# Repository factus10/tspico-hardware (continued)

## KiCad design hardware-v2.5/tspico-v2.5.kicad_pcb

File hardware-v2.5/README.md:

# TS-Pico v2.5 KiCad project

The v2.2 card (`../old/`, CircuitStudio, September 2023) redrawn all surface mount for JLCPCB assembly, on the v3 board outline (130 x 64.25 mm, 56 mm body plus the 8.25 mm tongue, same edge connector, 4 layers). The circuit, the designators and the Pico pin map are v2.2's, so the shipped firmware (tspico-firmware-build) runs unchanged. One block is new: bench programming of the flash from the Pico, so a board with a blank soldered flash can be loaded without a ROM programmer or a 2068.

**To order:** the JLCPCB upload files (Gerber zip, BOM, placement), ordering notes, schematic PDF and renders are on the [v2.5-proto1 release](https://github.com/factus10/tspico-hardware/releases/tag/v2.5-proto1). To regenerate them from this folder, run `python3 scripts/gen_fab.py` (output in `fab/jlcpcb/`).

Status 2026-10-11: schematic ERC clean and board DRC clean at every severity (no errors, no warnings, nothing unconnected); `scripts/check.sh` passes. Fully routed by `flow.py` on its first attempt with no hand edits: 2496 track segments and 406 vias (all 0.6/0.3 mm), every track on F.Cu or B.Cu, so both planes are unbroken; narrowest track 0.13 mm. Fab outputs (Gerbers, JLC BOM and CPL) are generated by `scripts/gen_fab.py`. Not built. JLC parts plus loading fees: $23.92 per board on a 10-board run, of which the Pico, flash and SRAM are $16.29.

## What changed from v2.2

| Part | v2.2 | v2.5 |
|---|---|---|
| U2 Pico | on socket headers | Raspberry Pi Pico module reflowed on its castellations (LCSC C7203002); a Pico 2 fits the footprint |
| U10 flash | SST39SF040 DIP-32 | SST39SF040 PLCC-32, soldered |
| U13 SRAM | AS6C4008 DIP-32 | CY62148ELL-55SXI (or AS6C4008-55SIN), 450 mil SOIC-32 |
| U1, U4, U5, U8, U9 | 74LS DIP | 74LS SOIC (same families: Pico 3.3 V outputs need TTL thresholds) |
| U6, U7 | 74LVC245 DIP | 74LVC245APW TSSOP-20 |
| U11 | TLC555 DIP | NE555 SOIC-8 (JLC preferred part, no loading fee) |
| Q1, D2 | 2N3904, SB260 | MMBT3904, SS14 |
| C2, C12, C16 | 10 uF electrolytic | 10 uF 25 V X5R 0805 (the 25 V rating keeps DC-bias loss small at 5 V, which matters for the 2.4 s reset timing cap C12) |
| U3 SD | SD breakout module | HRO TF-01A push-push socket (as v3), 10 k pull-ups on DAT1/DAT2 |
| SW1-SW3 | through-hole tactile | TS-1187A SMD tactile |
| JP1 (/BE link), P10 (flash write enable) | 2-pin header + shunt | solder jumper, closed as shipped (cut to open) |
| JP4 (port $00-$0F / $10-$1F) | 3-pin header | 3-pad solder jumper, 1-2 ($00-$0F) as shipped |
| JP2, JP3, JP5 (external NMI, TS reset, Pico reset buttons) | 2-pin headers | DNP SMD header pads |
| R12 | (rework on built boards, not in the 2023 schematic) | 4.7 k from U6 pin 8 (D6) to pin 10 (GND) |
| new | | R13/R14 10 k pull-ups on /ROSCS and /IORQ, R15/R16 10 k pull-ups on the flash and SRAM /CE (both deselected while the Pico boots) |
| new | | bench programming, below |

Everything JLCPCB assembles is SMT on the top side. Nothing through-hole is left.

## Bench programming the flash

The shipped firmware maps the 2068's HOME ROM from flash unconditionally at power-on (`src/dev_tspico.py`, `set_ctrl` started at line 5693), and `flash/README.md` says new boards get the 512K image burned with a programmer. A soldered blank flash would therefore leave the 2068 unable to boot, and the in-place `romupdate.tap` path needs a working ROM first. v2.2 has no free Pico GPIO to drive the flash address bus, so v2.5 adds a shift-register path that reuses existing pins:

- U12, U14, U15: 74HCT595 chain. SER = D1_L (GP3), SRCLK = D0_L (GP2) (the SPI0 pins already used for the SD card), RCLK = SD_CS (GP28). U12 drives A0-A7, U14 A8-A13, /RD and the flash /WE, U15 drives D0-D7 through RN1/RN2 (4.7 k). A14/A15 come from the Pico through U8 (R13 holds /ROSCS high off the bus), A16-A18 and /CE as in v2.2.
- Read-back for verify: U15's outputs high, /RD low, U6 enabled. R14 holds /IORQ high, so U6 points at the Pico, and the byte arrives on GP2-GP9. The 4.7 k series resistors let the flash win against U15.
- Power: SW4 (slide switch, RUN/PROG) in PROG puts the Pico's USB VBUS on the card's +5V through D3, so the memories and logic run with the card out of the computer.
- Enable: the 595 outputs are on only when SW4 is in PROG, VBUS is present, and there is no +15 V on edge pin B3 (Q2/Q3). Plugged into a powered 2068 they stay off whatever the switch says. In the 2068, SD traffic clocks garbage into the chain, but the outputs are disabled, so nothing reaches the bus.
- Procedure: card out of the 2068, SW4 to PROG, USB to the Pico, copy the 512K image to the Pico as `/flash.rom`, run `tools/benchprog.py` (draft, untested: chip erase, byte program, verify; a few minutes in MicroPython). SW4 back to RUN before the card goes into the computer.

The Z80-side `romupdate.tap` path works exactly as on v2.2 (P10 closed).

Things to keep in mind: with SW4 in PROG and USB plugged into a 2068 that is switched off, the USB port would try to power the 2068's 5 V rail (D3 conducts). The port's current limit protects the host, but keep SW4 in RUN except on the bench. The card's rail sits at about 4.7 V in PROG mode (USB minus a Schottky), which is inside the flash's 4.5-5.5 V range and fine for LS logic at bench temperatures.

## Files

| File | Purpose |
|---|---|
| `tspico-v2.5.kicad_pro`, `.kicad_sch`, `.kicad_pcb` | Project, root sheet, board. Sheets: `interface`, `logic`, `memory`, `pico`, `benchprog`. |
| `scripts/gen_schematic.py` | Generates the root sheet and the five sheets (netlist style: a global label on every pin, as in v3) and the project symbols (edge connector, plus corrected copies of the Pico, 74LVC245 and MMBT3904 stock symbols so ERC judges pin types correctly). Overwrites hand edits. |
| `scripts/parts.py` | (Value, footprint) to MPN and LCSC number, stamped on every symbol. Priced 2026-10-11 with `jlc_price.py`. |
| `scripts/gen_board.py`, `gen_edge_symbol.py` | Board skeleton and edge connector, shared geometry with v3 (`../hardware/README.md`). |
| `scripts/gen_layout.py` | Placement table, planes (In1 GND, In2 +5V; +3V3 is routed). Overwrites the board. |
| `scripts/flow.py`, `autoroute.py`, `finish.py`, `finish_route.py`, `silk.py` | The v3 routing flow (Freerouting 2.4.1, then clean-up and silkscreen), with v2.5's plane nets. |
| `scripts/gen_fab.py` | Gerbers, drill, JLC BOM and CPL into `fab/jlcpcb/`. |
| `scripts/check.sh` | ERC and DRC, fails on any violation. |
| `tools/benchprog.py` | Draft MicroPython bench programmer. |

```bash
cd hardware-v2.5
PY=/Applications/KiCad/KiCad.app/Contents/Frameworks/Python.framework/Versions/Current/bin/python3
python3 scripts/gen_schematic.py
$PY scripts/flow.py --jar <freerouting-2.4.1.jar>
python3 scripts/gen_fab.py
scripts/check.sh
```

## Layout

The Pico sits along the top left with its USB out of the left edge. Its GP0-GP15 row faces down toward the logic. Above it, left to right: SW4 and D3 by VBUS, D2/C2 by VSYS, then the Pico-side pull-ups. The buttons are along the top edge (SW1 NMI, SW2 TS reset, SW3 Pico reset), each with its DNP external-button pads. The SRAM and flash sit in the middle band, and the 555 reset is in the top-right corner. The micro SD is on the left edge below the Pico, its shell flush with the edge. The glue row (U1, U5, U4, U9, U8, U7) and the two address 595s (U12, U14) run across the board, with Q2/Q3 (the program-enable interlock) at its right end. U6 sits over the data fingers, and the data 595 (U15) with RN1/RN2 sits at the left end of the fingers. An earlier placement with U15 at the far end of the 595 row left one of its eight outputs unroutable twice.

Every used bottom-side finger (address, +15 V, +5 V, GND, /BE_IN) gets a locked B.Cu stub and a via 1.4 mm into the body (`gen_layout.py`); +5V gets two vias and a 0.5 mm stub into the In2 plane. Without them the router boxed in B4 (+5V) and B13 (A3).

## Before ordering

- Stock: U10 (C632847, 17 at JLC), U13 (C511135, 16), U9 (C7731, 56). Consign or swap if short; AS6C4008-55SIN fits U13's footprint and pinout.
- U13: check the CY62148E SOIC-32 pinout against the datasheet: /CE pin 22, /OE pin 24, /WE pin 29, VCC 32, GND 16. Address and data order do not matter for an SRAM only the Z80 sees.
- TF-01A footprint and card-detect: same open items as v3 (`../hardware/README.md`).
- JLC rotations for the PLCC, SOICs, Pico module and switches in the placement preview.

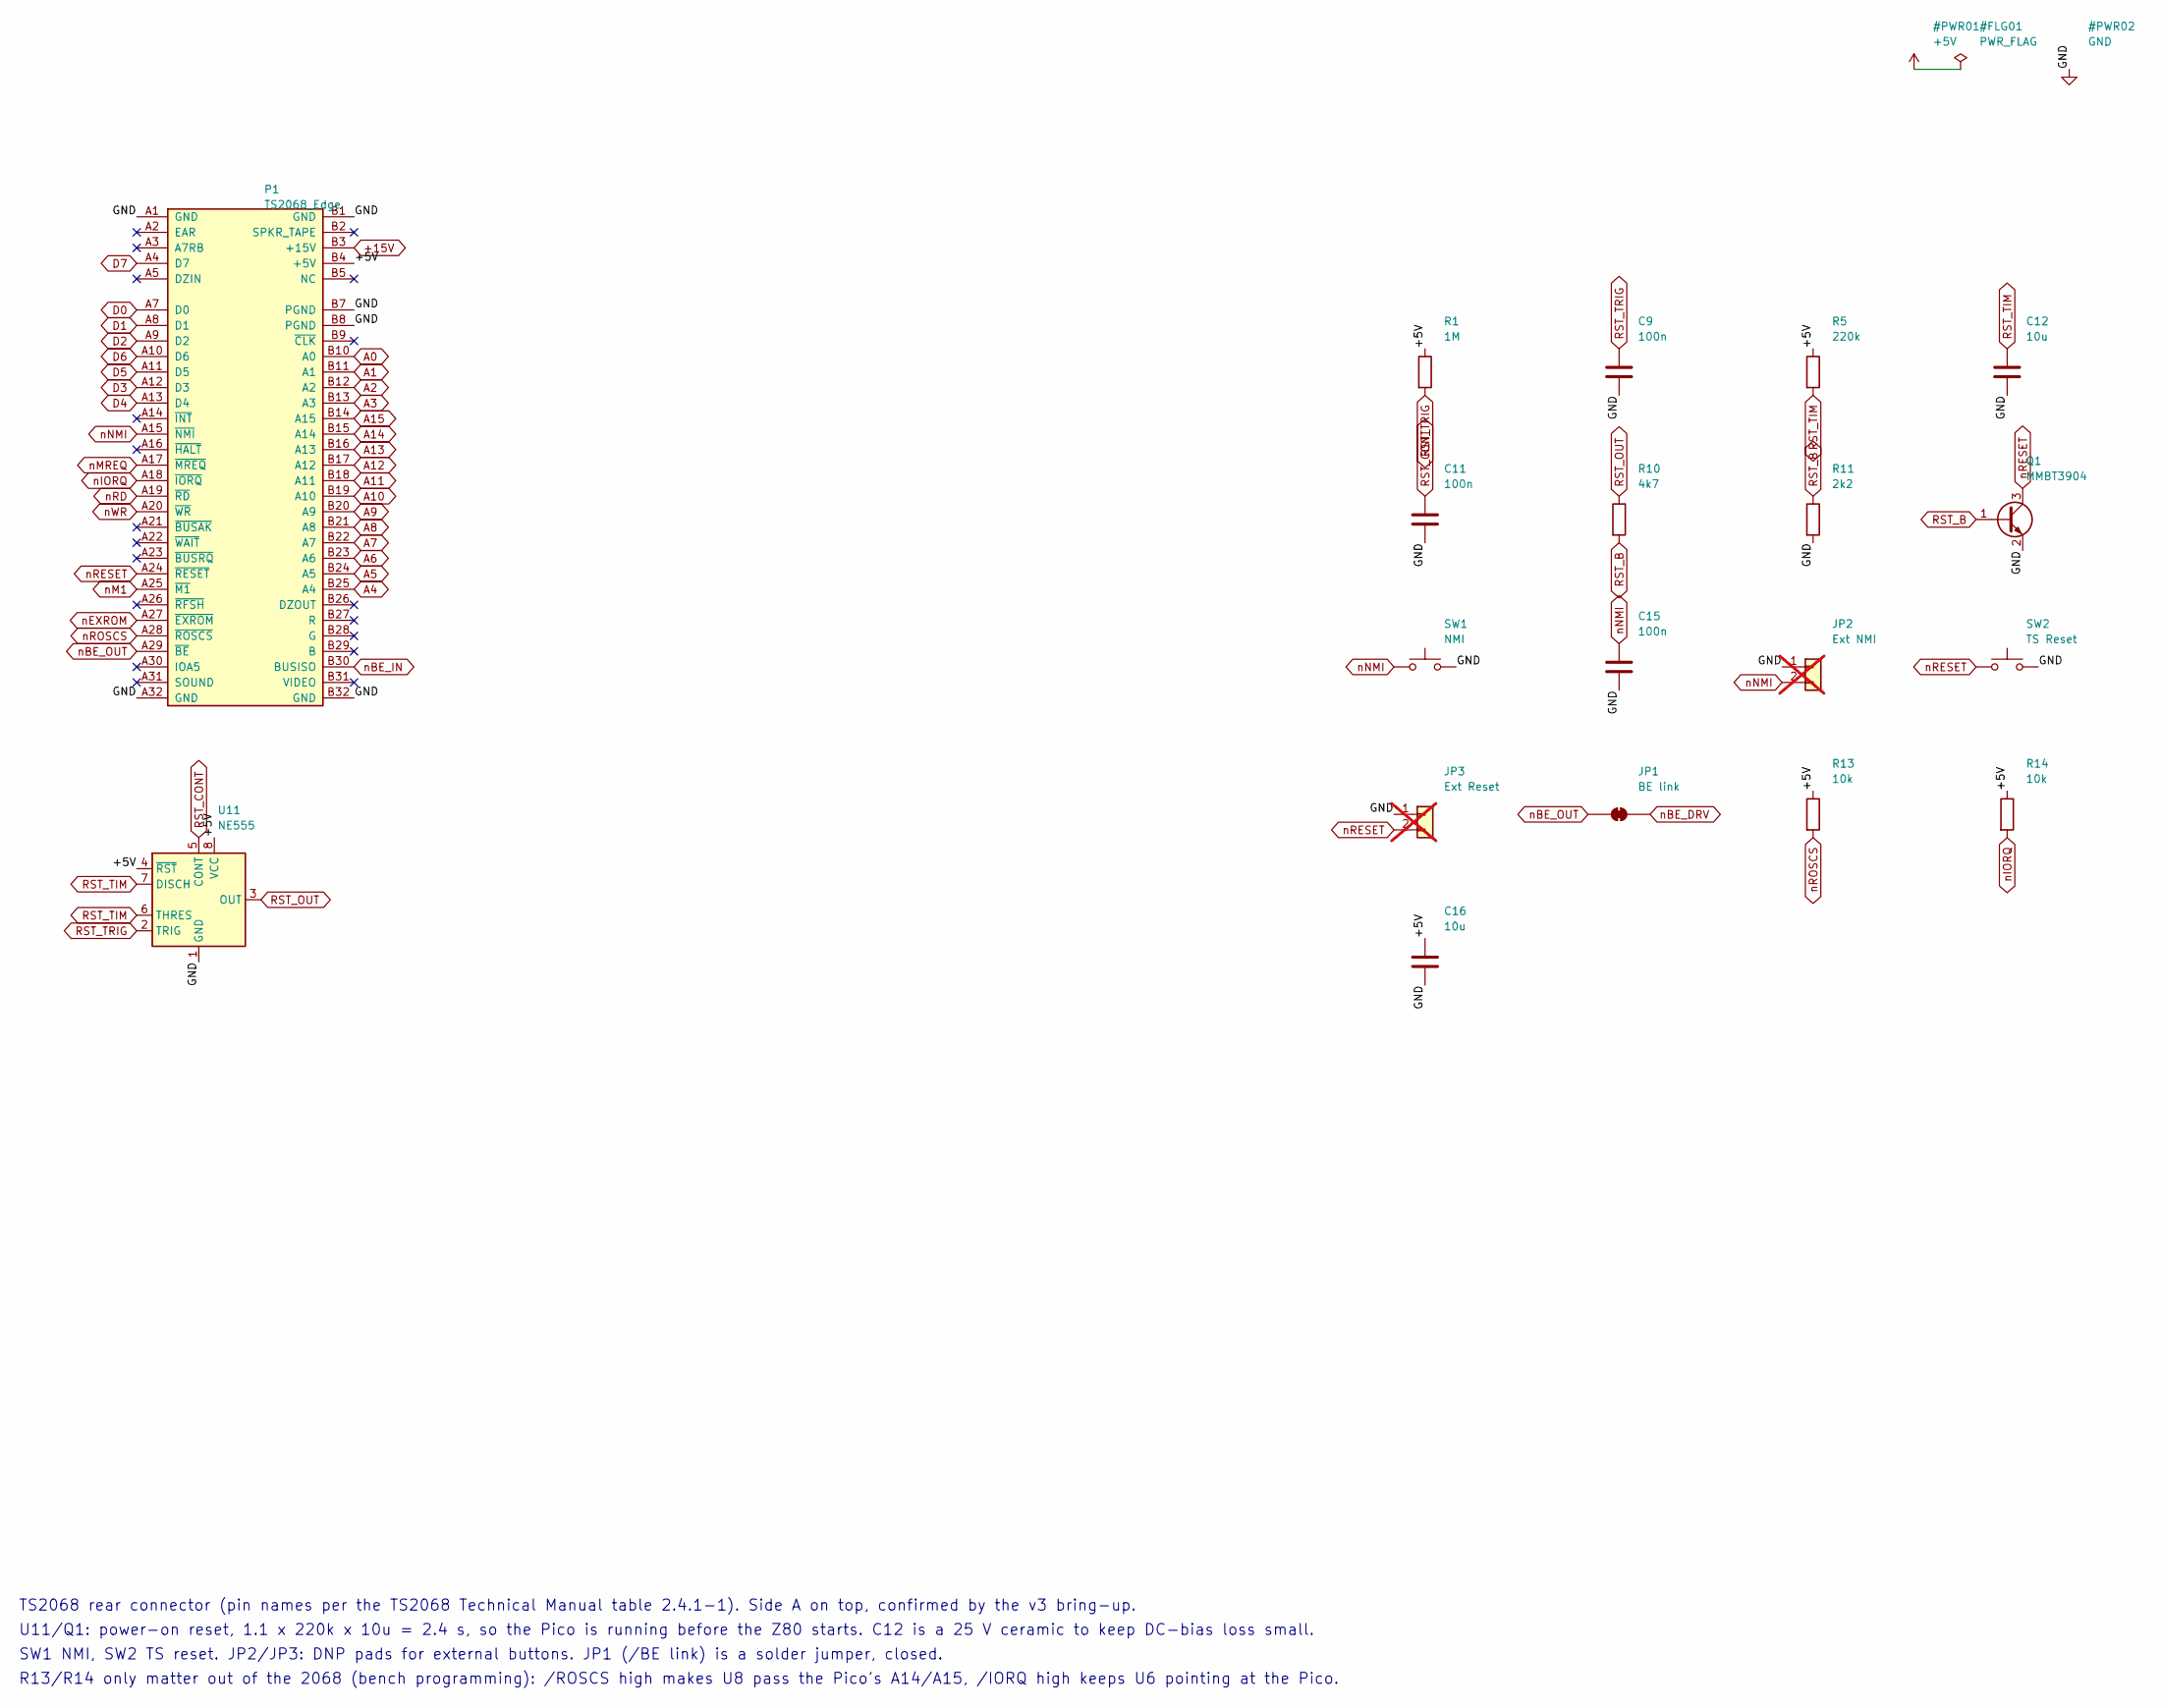
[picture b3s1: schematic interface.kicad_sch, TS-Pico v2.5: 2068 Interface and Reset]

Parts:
C9, C11, C15: 100n; C_0603_1608Metric; MPN CC0603KRX7R9BB104; LCSC C14663
C12, C16: 10u; C_0805_2012Metric; MPN CL21A106KAYNNNE; LCSC C15850
JP1: BE link; SolderJumper-2_P1.3mm_Bridged_RoundedPad1.0x1.5mm
JP2: Ext NMI; PinHeader_1x02_P2.54mm_Vertical_SMD_Pin1Left; not fitted
JP3: Ext Reset; PinHeader_1x02_P2.54mm_Vertical_SMD_Pin1Left; not fitted
P1: TS2068_Edge; TS2068_EdgeConnector_2x32
Q1: MMBT3904; SOT-23; MPN MMBT3904; LCSC C20526
R1: 1M; R_0603_1608Metric; MPN 0603WAF1004T5E; LCSC C22935
R5: 220k; R_0603_1608Metric; MPN 0603WAF2203T5E; LCSC C22961
R10: 4k7; R_0603_1608Metric; MPN 0603WAF4701T5E; LCSC C23162
R11: 2k2; R_0603_1608Metric; MPN 0603WAF2201T5E; LCSC C4190
R13, R14: 10k; R_0603_1608Metric; MPN 0603WAF1002T5E; LCSC C25804
SW1: NMI; SW_Push_1P1T_XKB_TS-1187A; MPN TS-1187A-B-A-B; LCSC C318884
SW2: TS Reset; SW_Push_1P1T_XKB_TS-1187A; MPN TS-1187A-B-A-B; LCSC C318884
U11: NE555; SOIC-8_3.9x4.9mm_P1.27mm; MPN NE555DR; LCSC C7593

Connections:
+5V: C16.1, P1.B4 (+5V), R1.1, R5.1, R13.1, R14.1, U11.4 (~RST), U11.8 (VCC); also elsewhere on the board
+15V: P1.B3 (+15V); also elsewhere on the board
A0: P1.B10 (A0); also elsewhere on the board
A1: P1.B11 (A1); also elsewhere on the board
A2: P1.B12 (A2); also elsewhere on the board
A3: P1.B13 (A3); also elsewhere on the board
A4: P1.B25 (A4); also elsewhere on the board
A5: P1.B24 (A5); also elsewhere on the board
A6: P1.B23 (A6); also elsewhere on the board
A7: P1.B22 (A7); also elsewhere on the board
A8: P1.B21 (A8); also elsewhere on the board
A9: P1.B20 (A9); also elsewhere on the board
A10: P1.B19 (A10); also elsewhere on the board
A11: P1.B18 (A11); also elsewhere on the board
A12: P1.B17 (A12); also elsewhere on the board
A13: P1.B16 (A13); also elsewhere on the board
A14: P1.B15 (A14); also elsewhere on the board
A15: P1.B14 (A15); also elsewhere on the board
D0: P1.A7 (D0); also elsewhere on the board
D1: P1.A8 (D1); also elsewhere on the board
D2: P1.A9 (D2); also elsewhere on the board
D3: P1.A12 (D3); also elsewhere on the board
D4: P1.A13 (D4); also elsewhere on the board
D5: P1.A11 (D5); also elsewhere on the board
D6: P1.A10 (D6); also elsewhere on the board
D7: P1.A4 (D7); also elsewhere on the board
GND: C9.2, C11.2, C12.2, C15.2, C16.2, JP2.1, JP3.1, P1.A1 (GND), P1.A32 (GND), P1.B1 (GND), P1.B7 (PGND), P1.B8 (PGND), P1.B32 (GND), Q1.2 (E), R11.2, SW1.2, SW2.2, U11.1 (GND); also elsewhere on the board
RST_B: Q1.1 (B), R10.2, R11.1
RST_CONT: C11.1, U11.5 (CONT)
RST_OUT: R10.1, U11.3 (OUT)
RST_TIM: C12.1, R5.2, U11.6 (THRES), U11.7 (DISCH)
RST_TRIG: C9.1, R1.2, U11.2 (TRIG)
nBE_DRV: JP1.2 (B); also elsewhere on the board
nBE_IN: P1.B30 (BUSISO); also elsewhere on the board
nBE_OUT: JP1.1 (A), P1.A29 (~BE)
nEXROM: P1.A27 (~EXROM); also elsewhere on the board
nIORQ: P1.A18 (~IORQ), R14.2; also elsewhere on the board
nM1: P1.A25 (~M1); also elsewhere on the board
nMREQ: P1.A17 (~MREQ); also elsewhere on the board
nNMI: C15.1, JP2.2, P1.A15 (~NMI), SW1.1
nRD: P1.A19 (~RD); also elsewhere on the board
nRESET: JP3.2, P1.A24 (~RESET), Q1.3 (C), SW2.1
nROSCS: P1.A28 (~ROSCS), R13.2; also elsewhere on the board
nWR: P1.A20 (~WR); also elsewhere on the board

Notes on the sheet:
TS2068 rear connector (pin names per the TS2068 Technical Manual table 2.4.1-1). Side A on top, confirmed by the v3 bring-up.
U11/Q1: power-on reset, 1.1 x 220k x 10u = 2.4 s, so the Pico is running before the Z80 starts. C12 is a 25 V ceramic to keep DC-bias loss small.
SW1 NMI, SW2 TS reset. JP2/JP3: DNP pads for external buttons. JP1 (/BE link) is a solder jumper, closed.
R13/R14 only matter out of the 2068 (bench programming): /ROSCS high makes U8 pass the Pico's A14/A15, /IORQ high keeps U6 pointing at the Pico.

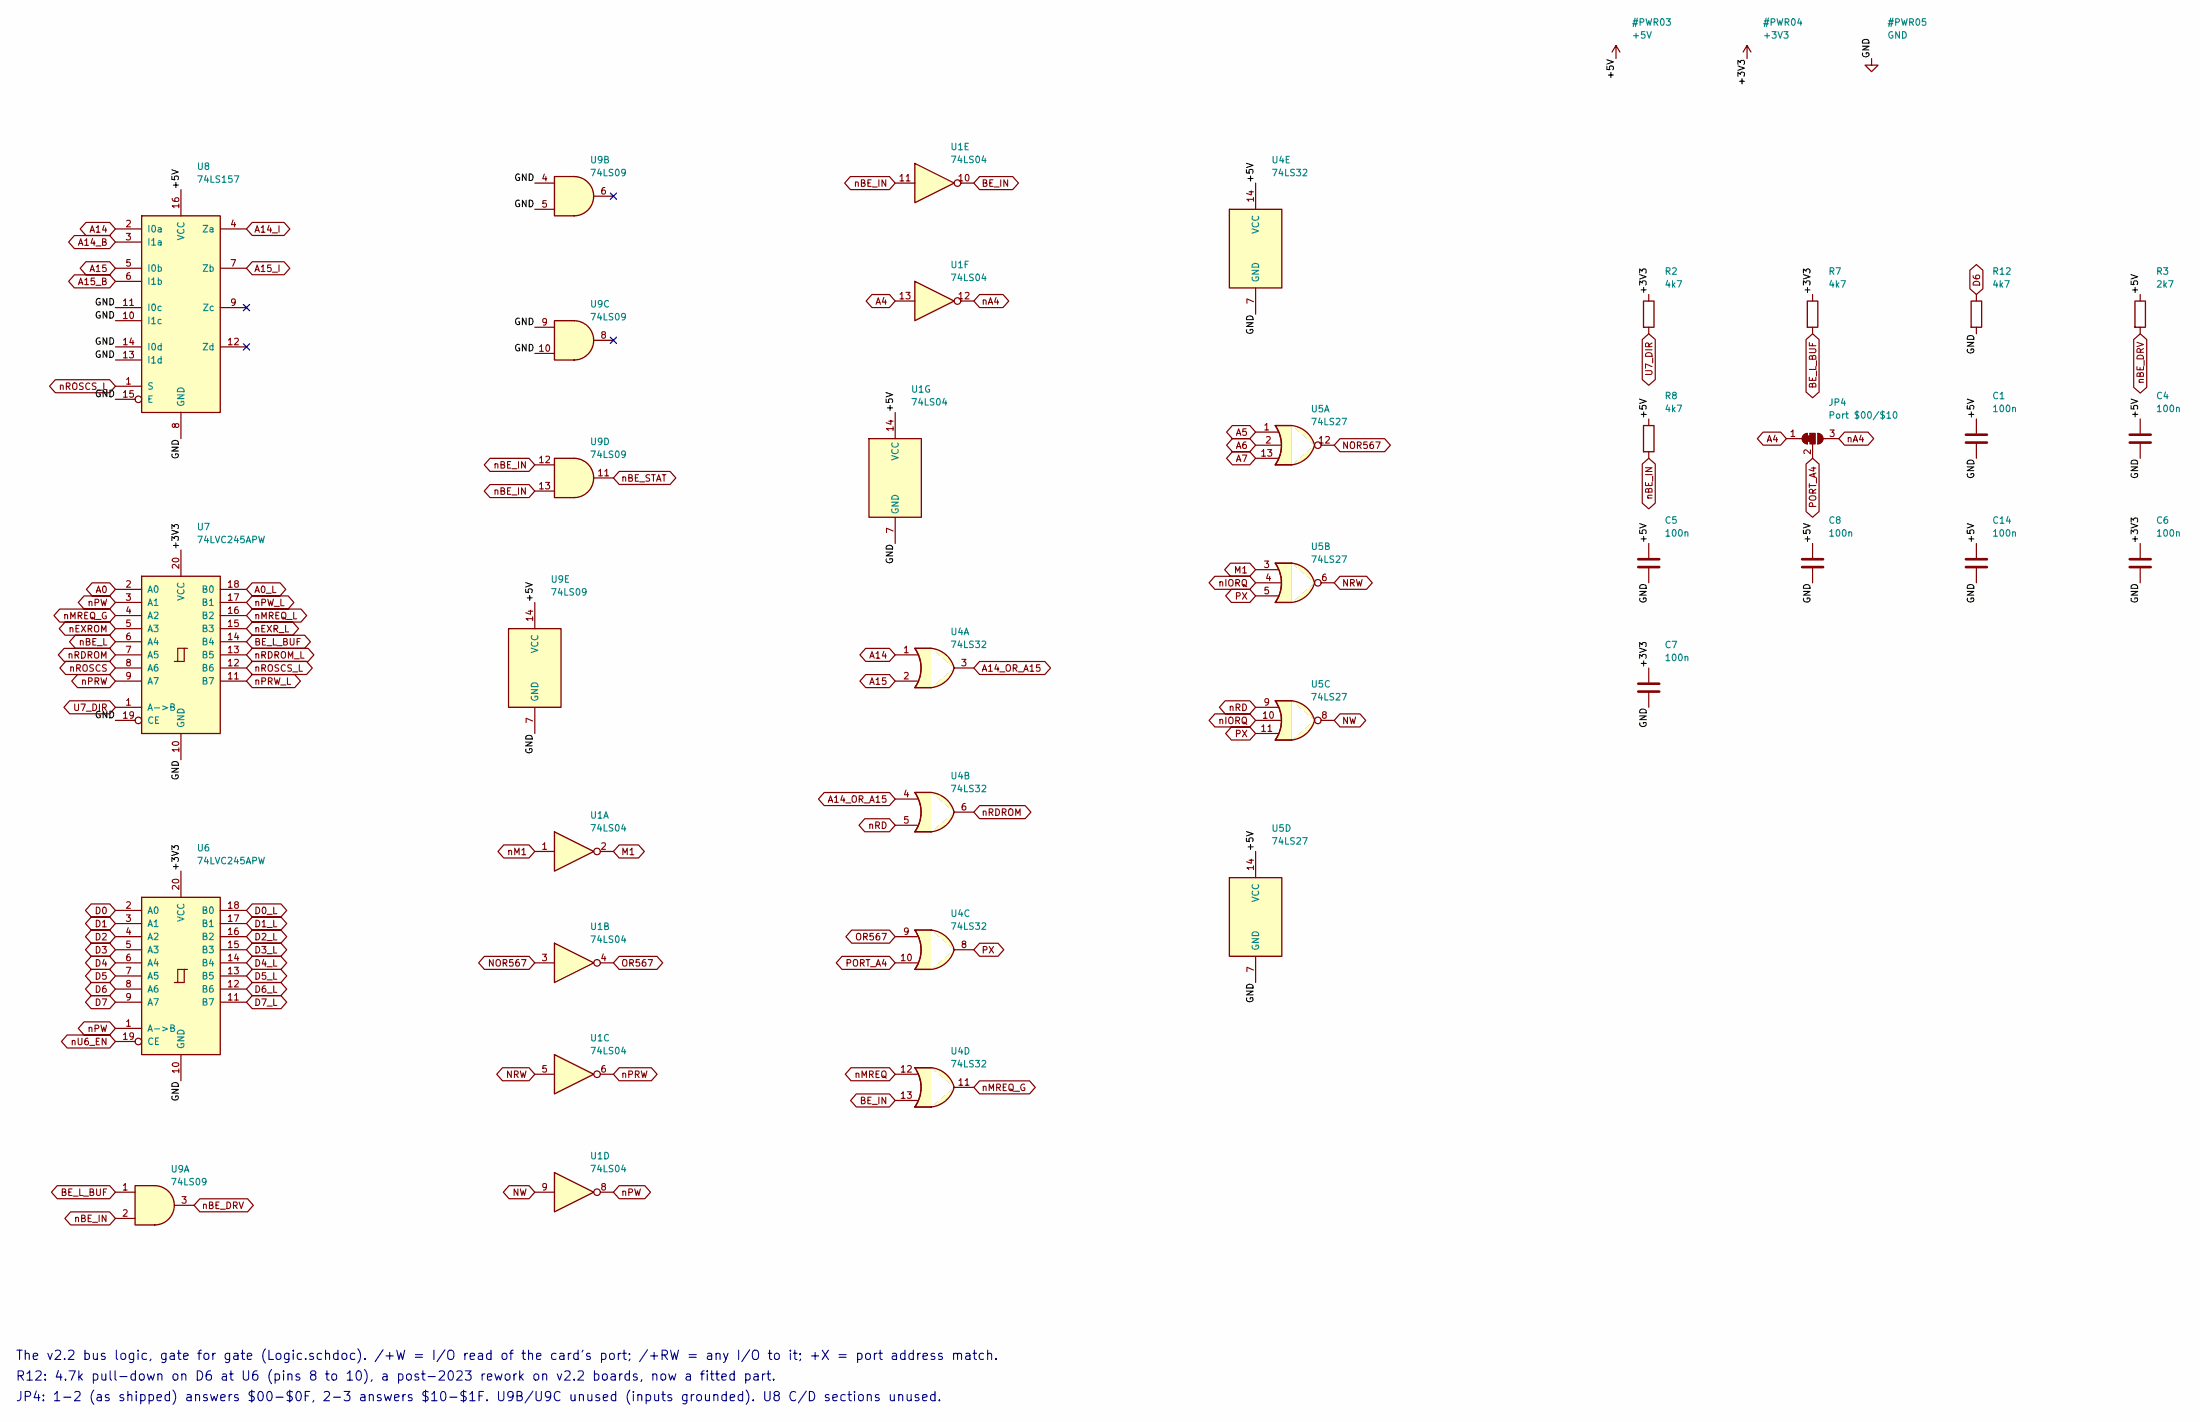
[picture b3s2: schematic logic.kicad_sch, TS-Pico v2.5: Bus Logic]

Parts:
C1, C4, C5, C6, C7, C8, C14: 100n; C_0603_1608Metric; MPN CC0603KRX7R9BB104; LCSC C14663
JP4: Port $00/$10; SolderJumper-3_P1.3mm_Bridged12_RoundedPad1.0x1.5mm_NumberL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
R2, R7, R8, R12: 4k7; R_0603_1608Metric; MPN 0603WAF4701T5E; LCSC C23162
R3: 2k7; R_0603_1608Metric; MPN 0603WAF2701T5E; LCSC C13167
U1: 74LS04; SOIC-14_3.9x8.7mm_P1.27mm; MPN SN74LS04DR; LCSC C6796
U4: 74LS32; SOIC-14_3.9x8.7mm_P1.27mm; MPN SN74LS32DR; LCSC C116812
U5: 74LS27; SOIC-14_3.9x8.7mm_P1.27mm; MPN XL74LS27; LCSC C707098
U6, U7: 74LVC245APW; TSSOP-20_4.4x6.5mm_P0.65mm; MPN 74LVC245APW,118; LCSC C6082
U8: 74LS157; SOIC-16_3.9x9.9mm_P1.27mm; MPN XL74LS157; LCSC C707097
U9: 74LS09; SOIC-14_3.9x8.7mm_P1.27mm; MPN SN74LS09DR; LCSC C7731

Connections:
+3V3: C6.1, C7.1, R2.1, R7.1, U6.20 (VCC), U7.20 (VCC); also elsewhere on the board
+5V: C1.1, C4.1, C5.1, C8.1, C14.1, R3.1, R8.1, U1.14 (VCC), U4.14 (VCC), U5.14 (VCC), U8.16 (VCC), U9.14 (VCC); also elsewhere on the board
A0: U7.2 (A0); also elsewhere on the board
A0_L: U7.18 (B0); also elsewhere on the board
A4: JP4.1 (A), U1.13; also elsewhere on the board
A5: U5.1; also elsewhere on the board
A6: U5.2; also elsewhere on the board
A7: U5.13; also elsewhere on the board
A14: U4.1, U8.2 (I0a); also elsewhere on the board
A14_B: U8.3 (I1a); also elsewhere on the board
A14_I: U8.4 (Za); also elsewhere on the board
A14_OR_A15: U4.3, U4.4
A15: U4.2, U8.5 (I0b); also elsewhere on the board
A15_B: U8.6 (I1b); also elsewhere on the board
A15_I: U8.7 (Zb); also elsewhere on the board
BE_IN: U1.10, U4.13
BE_L_BUF: R7.2, U7.14 (B4), U9.1
D0: U6.2 (A0); also elsewhere on the board
D0_L: U6.18 (B0); also elsewhere on the board
D1: U6.3 (A1); also elsewhere on the board
D1_L: U6.17 (B1); also elsewhere on the board
D2: U6.4 (A2); also elsewhere on the board
D2_L: U6.16 (B2); also elsewhere on the board
D3: U6.5 (A3); also elsewhere on the board
D3_L: U6.15 (B3); also elsewhere on the board
D4: U6.6 (A4); also elsewhere on the board
D4_L: U6.14 (B4); also elsewhere on the board
D5: U6.7 (A5); also elsewhere on the board
D5_L: U6.13 (B5); also elsewhere on the board
D6: R12.1, U6.8 (A6); also elsewhere on the board
D6_L: U6.12 (B6); also elsewhere on the board
D7: U6.9 (A7); also elsewhere on the board
D7_L: U6.11 (B7); also elsewhere on the board
GND: C1.2, C4.2, C5.2, C6.2, C7.2, C8.2, C14.2, R12.2, U1.7 (GND), U4.7 (GND), U5.7 (GND), U6.10 (GND), U7.10 (GND), U7.19 (CE), U8.8 (GND), U8.10 (I1c), U8.11 (I0c), U8.13 (I1d), U8.14 (I0d), U8.15 (E), U9.4, U9.5, U9.7 (GND), U9.9, U9.10; also elsewhere on the board
M1: U1.2, U5.3
NOR567: U1.3, U5.12
NRW: U1.5, U5.6
NW: U1.9, U5.8
OR567: U1.4, U4.9
PORT_A4: JP4.2 (C), U4.10
PX: U4.8, U5.5, U5.11
U7_DIR: R2.2, U7.1 (A->B)
nA4: JP4.3 (B), U1.12
nBE_DRV: R3.2, U9.3; also elsewhere on the board
nBE_IN: R8.2, U1.11, U9.2, U9.12, U9.13; also elsewhere on the board
nBE_L: U7.6 (A4); also elsewhere on the board
nBE_STAT: U9.11; also elsewhere on the board
nEXROM: U7.5 (A3); also elsewhere on the board
nEXR_L: U7.15 (B3); also elsewhere on the board
nIORQ: U5.4, U5.10; also elsewhere on the board
nM1: U1.1; also elsewhere on the board
nMREQ: U4.12; also elsewhere on the board
nMREQ_G: U4.11, U7.4 (A2)
nMREQ_L: U7.16 (B2); also elsewhere on the board
nPRW: U1.6, U7.9 (A7)
nPRW_L: U7.11 (B7); also elsewhere on the board
nPW: U1.8, U6.1 (A->B), U7.3 (A1)
nPW_L: U7.17 (B1); also elsewhere on the board
nRD: U4.5, U5.9; also elsewhere on the board
nRDROM: U4.6, U7.7 (A5)
nRDROM_L: U7.13 (B5); also elsewhere on the board
nROSCS: U7.8 (A6); also elsewhere on the board
nROSCS_L: U7.12 (B6), U8.1 (S); also elsewhere on the board
nU6_EN: U6.19 (CE); also elsewhere on the board

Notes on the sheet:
The v2.2 bus logic, gate for gate (Logic.schdoc). /+W = I/O read of the card's port; /+RW = any I/O to it; +X = port address match.
R12: 4.7k pull-down on D6 at U6 (pins 8 to 10), a post-2023 rework on v2.2 boards, now a fitted part.
JP4: 1-2 (as shipped) answers $00-$0F, 2-3 answers $10-$1F. U9B/U9C unused (inputs grounded). U8 C/D sections unused.

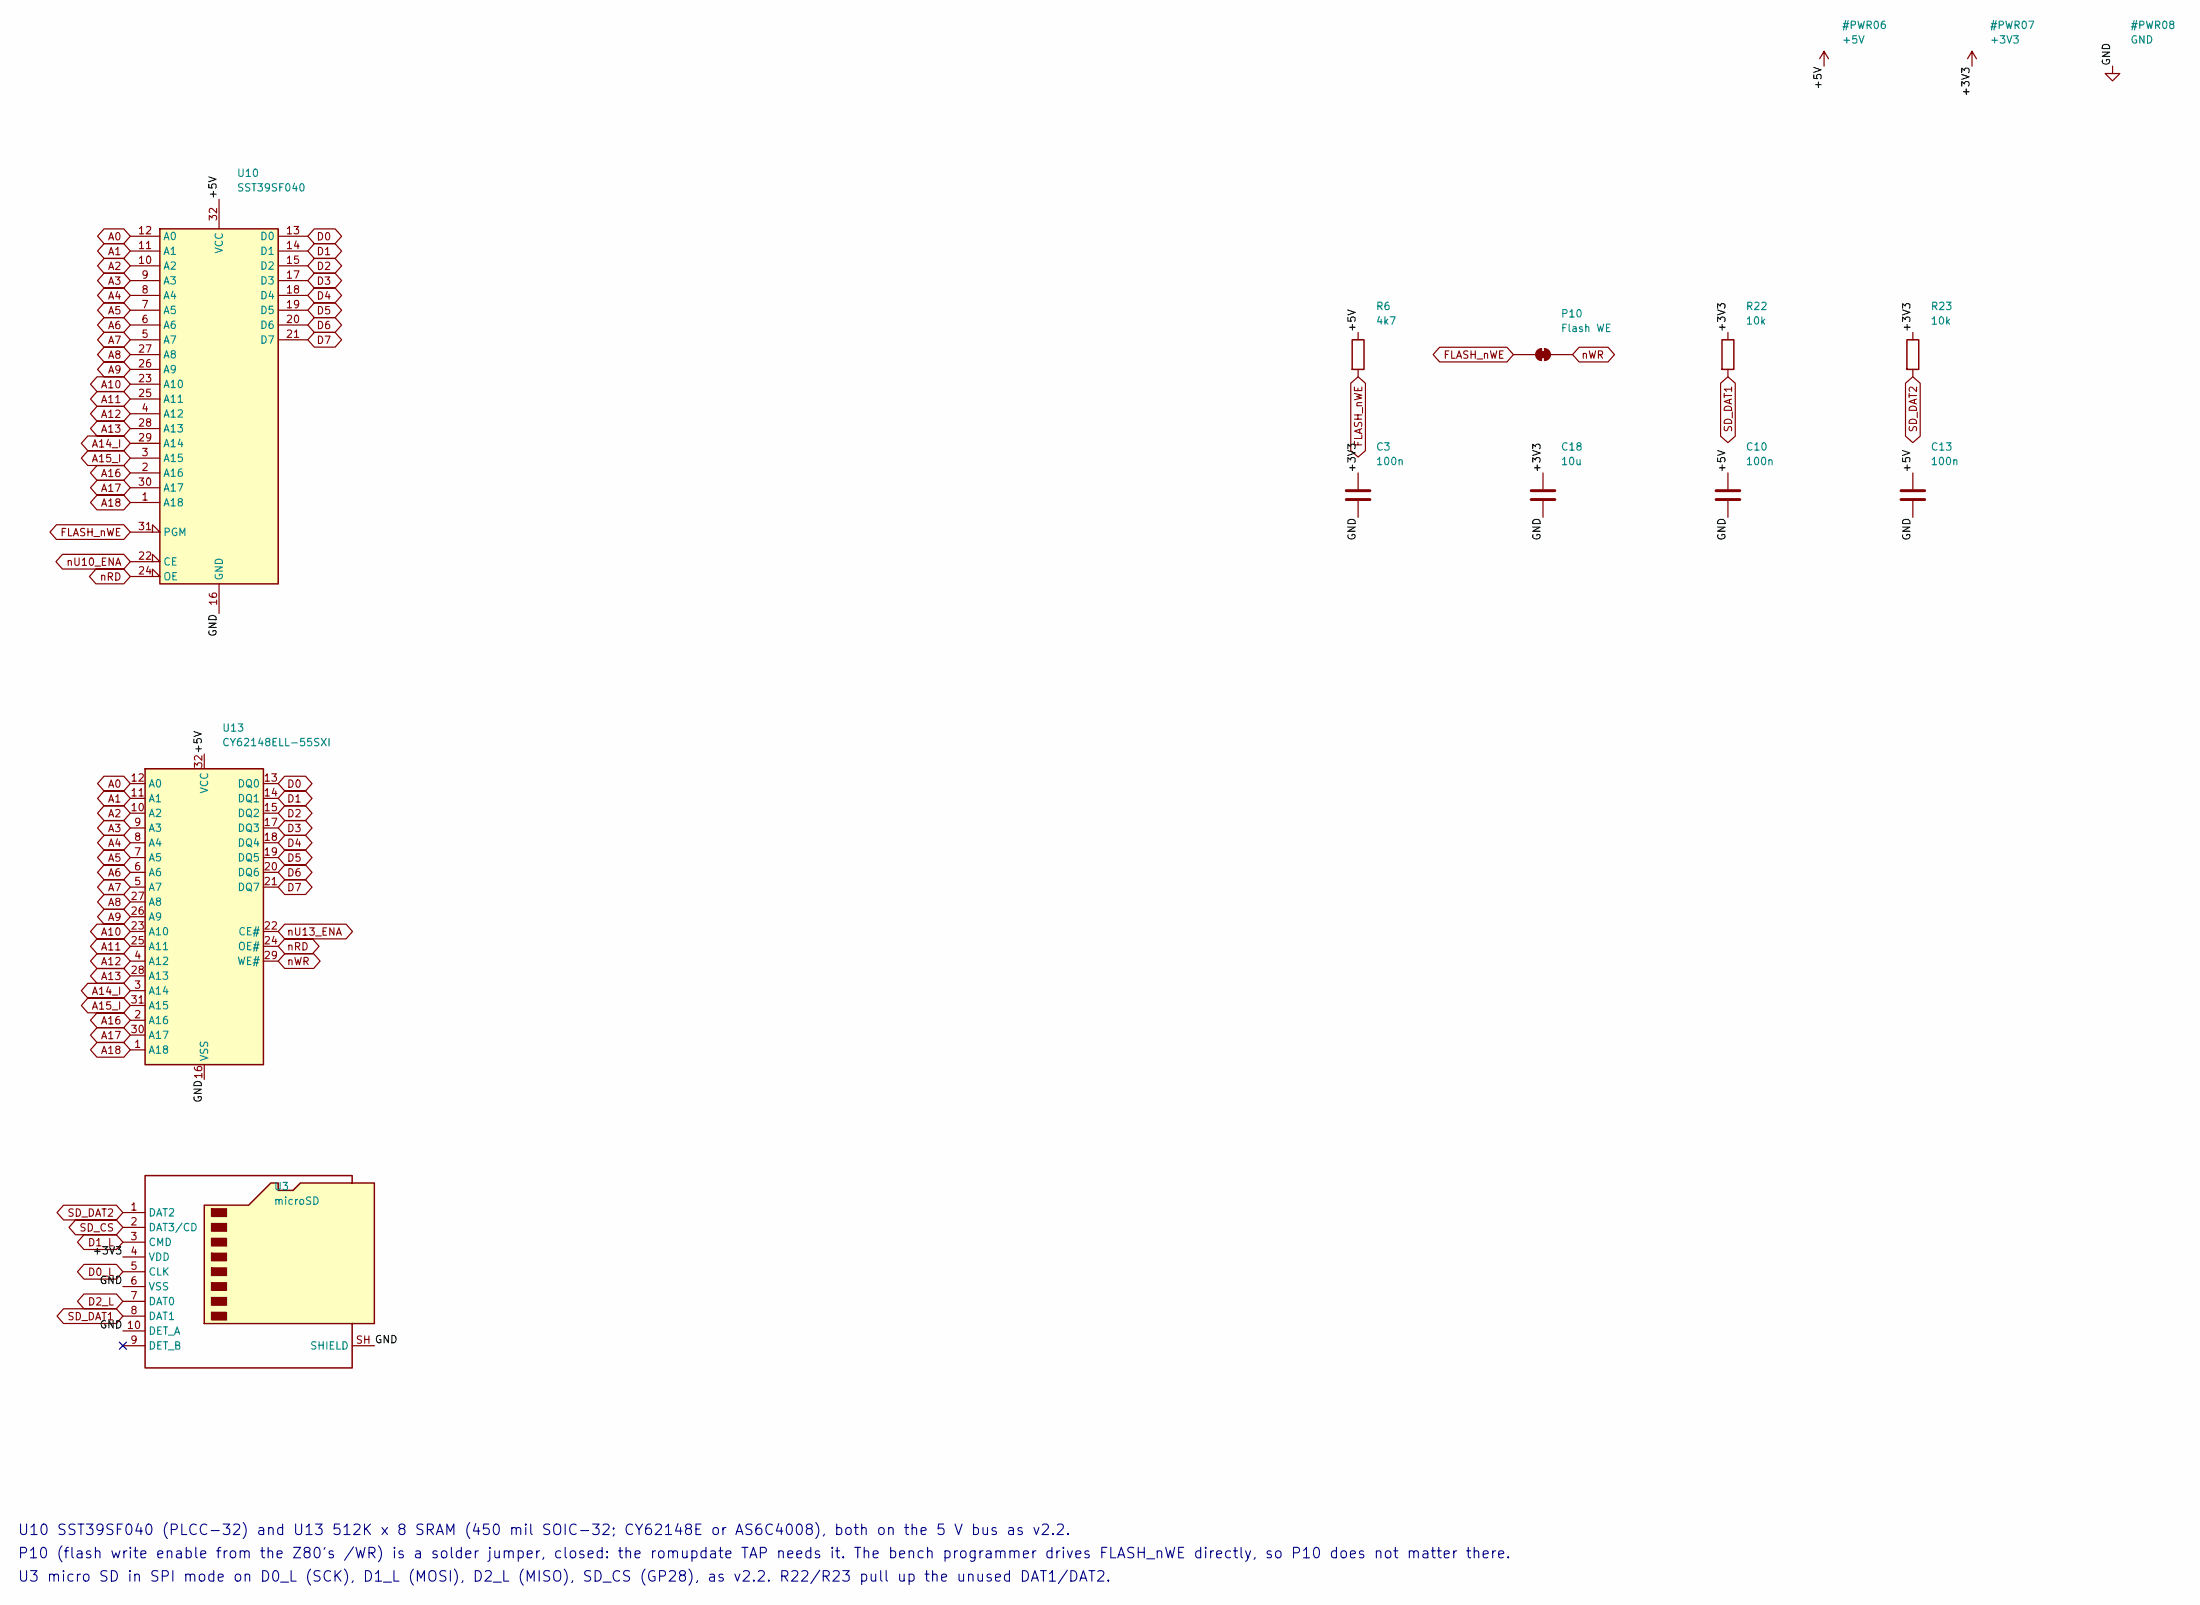
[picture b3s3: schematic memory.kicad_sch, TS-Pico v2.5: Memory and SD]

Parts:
C3, C10, C13: 100n; C_0603_1608Metric; MPN CC0603KRX7R9BB104; LCSC C14663
C18: 10u; C_0805_2012Metric; MPN CL21A106KAYNNNE; LCSC C15850
P10: Flash WE; SolderJumper-2_P1.3mm_Bridged_RoundedPad1.0x1.5mm
R6: 4k7; R_0603_1608Metric; MPN 0603WAF4701T5E; LCSC C23162
R22, R23: 10k; R_0603_1608Metric; MPN 0603WAF1002T5E; LCSC C25804
U3: microSD; microSD_TF-01A; MPN TF-01A; LCSC C91145
U10: SST39SF040; PLCC-32_11.4x14.0mm_P1.27mm; MPN SST39SF040-55-4I-NHE-T; LCSC C632847
U13: CY62148ELL-55SXI; SOP-32_11.305x20.495mm_P1.27mm; MPN CY62148ELL-55SXIT; LCSC C511135

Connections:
+3V3: C3.1, C18.1, R22.1, R23.1, U3.4 (VDD); also elsewhere on the board
+5V: C10.1, C13.1, R6.1, U10.32 (VCC), U13.32 (VCC); also elsewhere on the board
A0: U10.12 (A0), U13.12 (A0); also elsewhere on the board
A1: U10.11 (A1), U13.11 (A1); also elsewhere on the board
A2: U10.10 (A2), U13.10 (A2); also elsewhere on the board
A3: U10.9 (A3), U13.9 (A3); also elsewhere on the board
A4: U10.8 (A4), U13.8 (A4); also elsewhere on the board
A5: U10.7 (A5), U13.7 (A5); also elsewhere on the board
A6: U10.6 (A6), U13.6 (A6); also elsewhere on the board
A7: U10.5 (A7), U13.5 (A7); also elsewhere on the board
A8: U10.27 (A8), U13.27 (A8); also elsewhere on the board
A9: U10.26 (A9), U13.26 (A9); also elsewhere on the board
A10: U10.23 (A10), U13.23 (A10); also elsewhere on the board
A11: U10.25 (A11), U13.25 (A11); also elsewhere on the board
A12: U10.4 (A12), U13.4 (A12); also elsewhere on the board
A13: U10.28 (A13), U13.28 (A13); also elsewhere on the board
A14_I: U10.29 (A14), U13.3 (A14); also elsewhere on the board
A15_I: U10.3 (A15), U13.31 (A15); also elsewhere on the board
A16: U10.2 (A16), U13.2 (A16); also elsewhere on the board
A17: U10.30 (A17), U13.30 (A17); also elsewhere on the board
A18: U10.1 (A18), U13.1 (A18); also elsewhere on the board
D0: U10.13 (D0), U13.13 (DQ0); also elsewhere on the board
D0_L: U3.5 (CLK); also elsewhere on the board
D1: U10.14 (D1), U13.14 (DQ1); also elsewhere on the board
D1_L: U3.3 (CMD); also elsewhere on the board
D2: U10.15 (D2), U13.15 (DQ2); also elsewhere on the board
D2_L: U3.7 (DAT0); also elsewhere on the board
D3: U10.17 (D3), U13.17 (DQ3); also elsewhere on the board
D4: U10.18 (D4), U13.18 (DQ4); also elsewhere on the board
D5: U10.19 (D5), U13.19 (DQ5); also elsewhere on the board
D6: U10.20 (D6), U13.20 (DQ6); also elsewhere on the board
D7: U10.21 (D7), U13.21 (DQ7); also elsewhere on the board
FLASH_nWE: P10.1 (A), R6.2, U10.31 (PGM); also elsewhere on the board
GND: C3.2, C10.2, C13.2, C18.2, U3.6 (VSS), U3.10 (DET_A), U3.SH (SHIELD), U10.16 (GND), U13.16 (VSS); also elsewhere on the board
SD_CS: U3.2 (DAT3/CD); also elsewhere on the board
SD_DAT1: R22.2, U3.8 (DAT1)
SD_DAT2: R23.2, U3.1 (DAT2)
nRD: U10.24 (OE), U13.24 (OE#); also elsewhere on the board
nU10_ENA: U10.22 (CE); also elsewhere on the board
nU13_ENA: U13.22 (CE#); also elsewhere on the board
nWR: P10.2 (B), U13.29 (WE#); also elsewhere on the board

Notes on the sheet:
U10 SST39SF040 (PLCC-32) and U13 512K x 8 SRAM (450 mil SOIC-32; CY62148E or AS6C4008), both on the 5 V bus as v2.2.
P10 (flash write enable from the Z80's /WR) is a solder jumper, closed: the romupdate TAP needs it. The bench programmer drives FLASH_nWE directly, so P10 does not matter there.
U3 micro SD in SPI mode on D0_L (SCK), D1_L (MOSI), D2_L (MISO), SD_CS (GP28), as v2.2. R22/R23 pull up the unused DAT1/DAT2.
